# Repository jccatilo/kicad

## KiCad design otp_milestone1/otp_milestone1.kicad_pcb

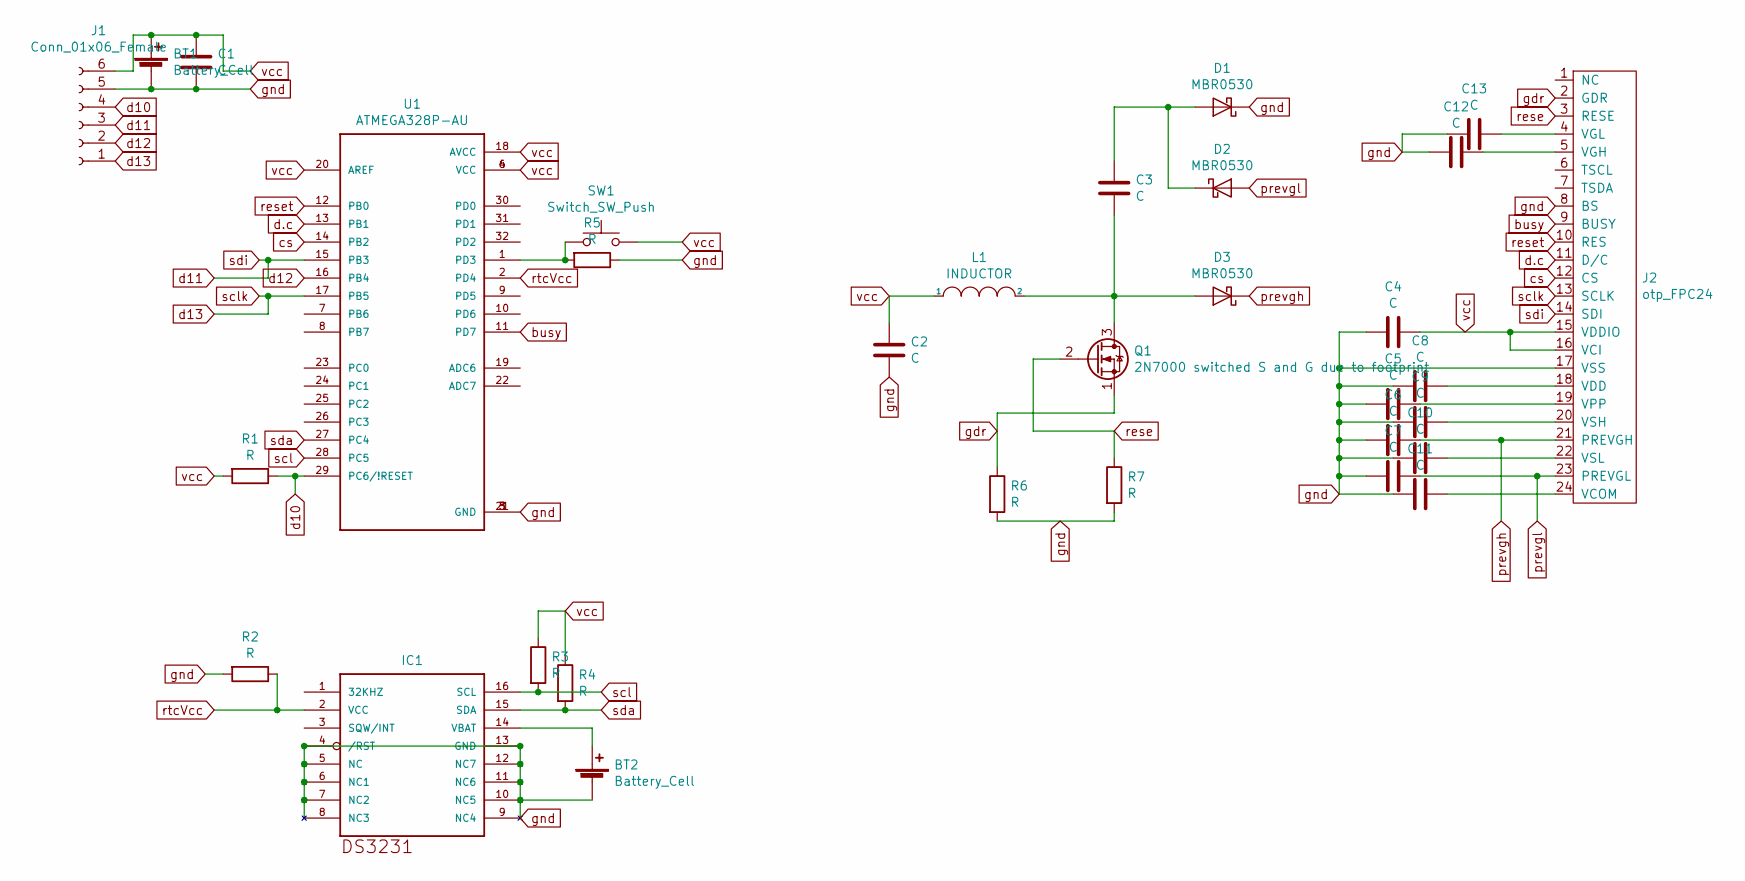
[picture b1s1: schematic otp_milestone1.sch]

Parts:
BT1: Battery_Cell; otp_coincellbattery holder
BT2: Battery_Cell; Conn2
C1, C2, C3, C4, C5, C6, C7, C8, C9, C10, C11, C12, C13: C; C_0805_HandSoldering
D1, D2, D3: MBR0530; D_2010
IC1: DS3231; SO16W
J1: Conn_01x06_Female; conn6
J2: otp_FPC24; FPC24
L1: INDUCTOR; inductorsmd
Q1: 2N7000 switched S and G due to footprint; SOT-23
R1, R2, R3, R4, R5, R6, R7: R; R_0805_HandSoldering
SW1: Switch_SW_Push; pushbutton_2pin
U1: ATMEGA328P-AU; QFP80P900X900X120-32N

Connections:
unnamed: BT2.1 (+), IC1.14 (VBAT)
unnamed: C3.1, D1.2 (A), D2.1 (K)
unnamed: C3.2, D3.2 (A), L1.2, Q1.3 (D)
unnamed: C5.1, J2.19 (VPP)
unnamed: C8.1, J2.18 (VDD)
unnamed: C9.1, J2.20 (VSH)
unnamed: C10.1, J2.22 (VSL)
unnamed: C11.1, J2.24 (VCOM)
unnamed: C12.1, J2.5 (VGH)
unnamed: C13.1, J2.4 (VGL)
unnamed: R5.2, SW1.1, U1.1 (PD3)
busy: J2.9 (BUSY), U1.11 (PD7)
cs: J2.12 (CS), U1.14 (PB2)
d10: J1.4, R1.1, U1.29 (PC6/!RESET)
d11: J1.3, J2.14 (SDI), U1.15 (PB3)
d12: J1.2, U1.16 (PB4)
d13: J1.1, J2.13 (SCLK), U1.17 (PB5)
d.c: J2.11 (D/C), U1.13 (PB1)
gdr: J2.2 (GDR), Q1.1 (S), R6.1
gnd: BT1.2 (-), BT2.2 (-), C1.2, C2.2, C4.2, C5.2, C6.2, C7.2, C8.2, C9.2, C10.2, C11.2, C12.2, C13.2, D1.1 (K), IC1.4 (/RST), IC1.5 (NC), IC1.6 (NC1), IC1.7 (NC2), IC1.8 (NC3), IC1.9 (NC4), IC1.10 (NC5), IC1.11 (NC6), IC1.12 (NC7), IC1.13 (GND), J1.5, J2.8 (BS), J2.17 (VSS), R2.2, R5.1, R6.2, R7.2, U1.3 (GND), U1.5 (GND), U1.21 (GND)
prevgh: C6.1, D3.1 (K), J2.21 (PREVGH)
prevgl: C7.1, D2.2 (A), J2.23 (PREVGL)
rese: J2.3 (RESE), Q1.2 (G), R7.1
reset: J2.10 (RES), U1.12 (PB0)
rtcVcc: IC1.2 (VCC), R2.1, U1.2 (PD4)
scl: IC1.16 (SCL), R3.2, U1.28 (PC5)
sda: IC1.15 (SDA), R4.2, U1.27 (PC4)
vcc: BT1.1 (+), C1.1, C2.1, C4.1, J1.6, J2.15 (VDDIO), J2.16 (VCI), L1.1, R1.2, R3.1, R4.1, SW1.2, U1.4 (VCC), U1.6 (VCC), U1.18 (AVCC), U1.20 (AREF)

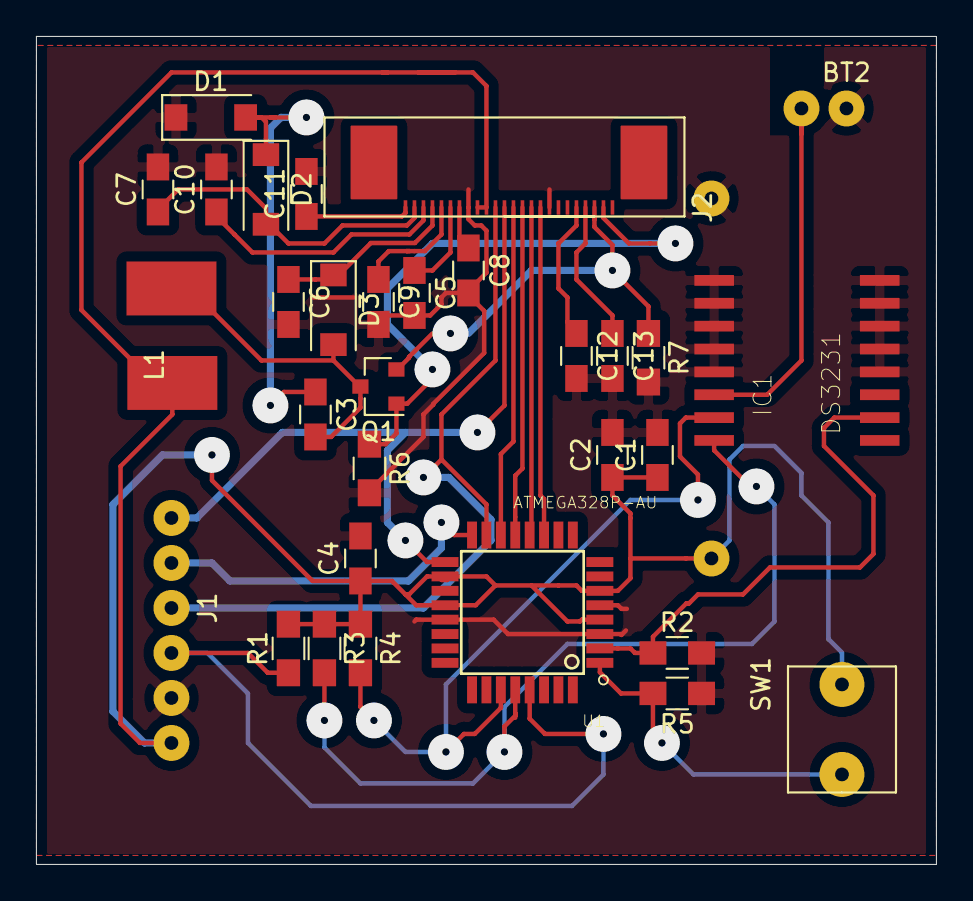
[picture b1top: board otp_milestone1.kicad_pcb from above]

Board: 2 copper layers, 50.0 x 46.0 mm, 32 parts (0 on the bottom side), 28 nets.

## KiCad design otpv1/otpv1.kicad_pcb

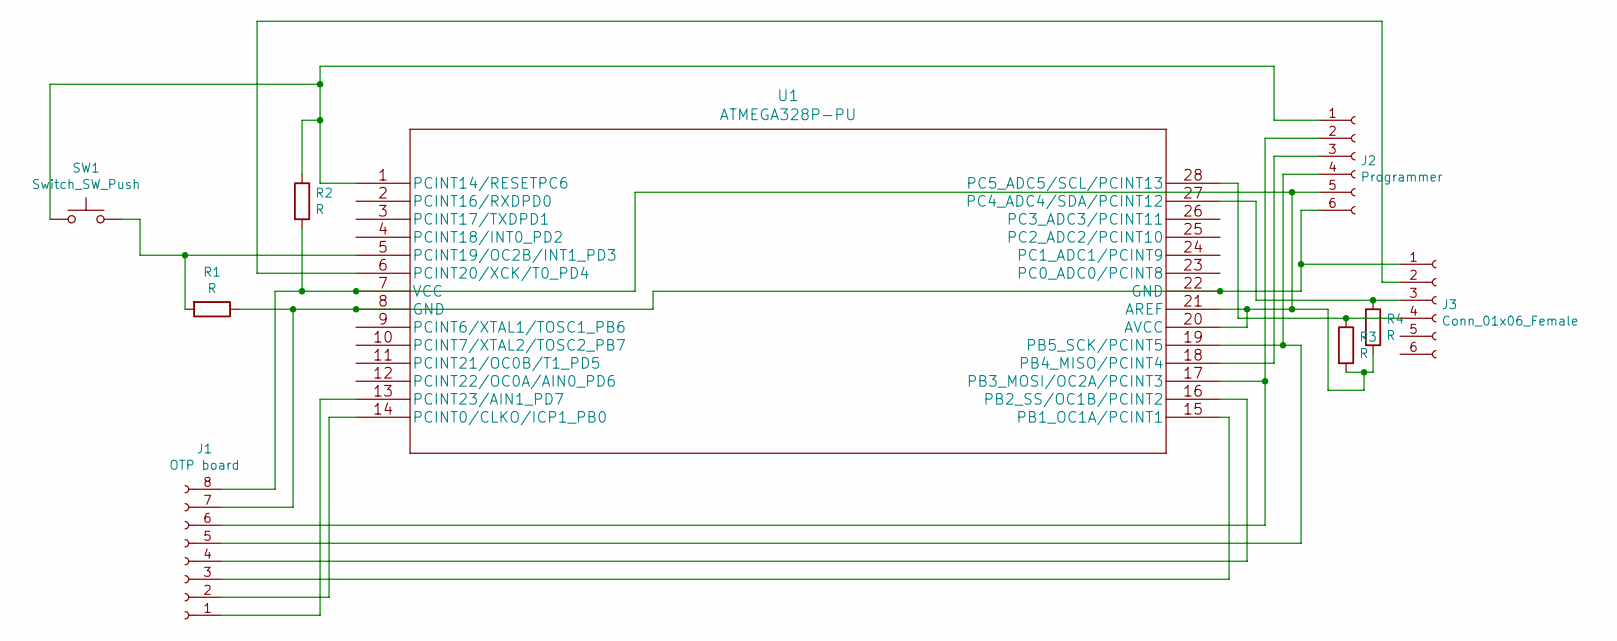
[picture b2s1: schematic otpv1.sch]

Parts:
J1: OTP board; conn8
J2: Programmer; conn6
J3: Conn_01x06_Female; conn6
R1, R2, R3, R4: R; R_0805_HandSoldering
SW1: Switch_SW_Push; pushbutton
U1: ATMEGA328P-PU

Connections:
unnamed: J1.1, U1.13 (PCINT23/AIN1_PD7)
unnamed: J1.2, U1.14 (PCINT0/CLKO/ICP1_PB0)
unnamed: J1.3, U1.15 (PB1_OC1A/PCINT1)
unnamed: J1.4, U1.16 (PB2_SS/OC1B/PCINT2)
unnamed: J1.5, J2.4, U1.19 (PB5_SCK/PCINT5)
unnamed: J1.6, J2.2, U1.17 (PB3_MOSI/OC2A/PCINT3)
unnamed: J1.7, J2.6, J3.1, R1.1, U1.8 (GND), U1.22 (GND)
unnamed: J1.8, J2.5, R2.2, R3.2, R4.2, U1.7 (VCC), U1.20 (AVCC), U1.21 (AREF)
unnamed: J2.1, R2.1, SW1.1, U1.1 (PCINT14/RESETPC6)
unnamed: J2.3, U1.18 (PB4_MISO/PCINT4)
unnamed: J3.2, U1.6 (PCINT20/XCK/T0_PD4)
unnamed: J3.3, R4.1, U1.27 (PC4_ADC4/SDA/PCINT12)
unnamed: J3.4, R3.1, U1.28 (PC5_ADC5/SCL/PCINT13)
unnamed: R1.2, SW1.2, U1.5 (PCINT19/OC2B/INT1_PD3)

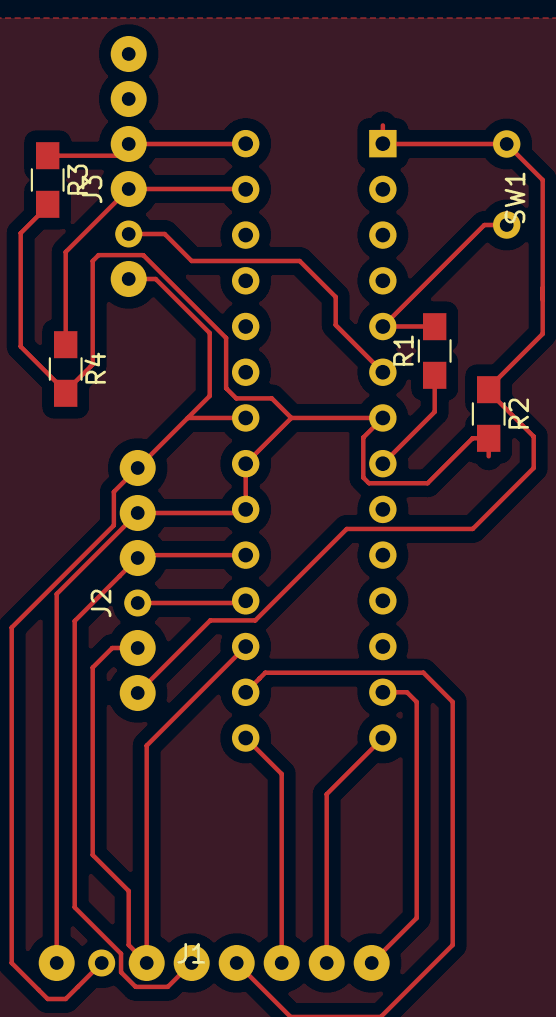
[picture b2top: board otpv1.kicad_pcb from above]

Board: 2 copper layers, 9 parts (1 on the bottom side), 14 nets.

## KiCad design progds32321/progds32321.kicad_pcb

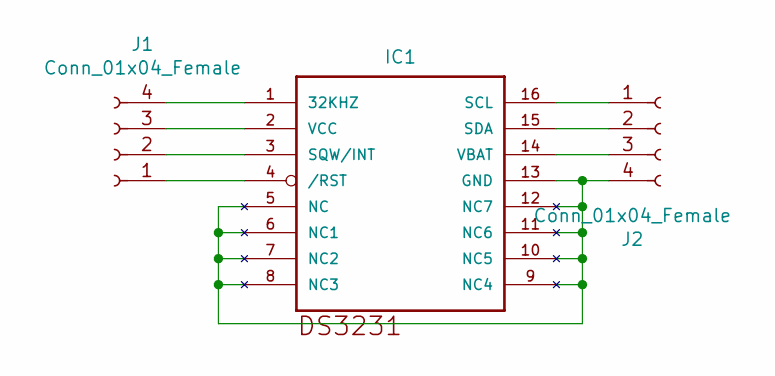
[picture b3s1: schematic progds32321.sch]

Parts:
IC1: DS3231; SO16W
J1, J2: Conn_01x04_Female; Connector4

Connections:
unnamed: IC1.1 (32KHZ), J1.4
unnamed: IC1.2 (VCC), J1.3
unnamed: IC1.3 (SQW/INT), J1.2
unnamed: IC1.4 (/RST), J1.1
unnamed: IC1.5 (NC), IC1.6 (NC1), IC1.7 (NC2), IC1.8 (NC3), IC1.9 (NC4), IC1.10 (NC5), IC1.11 (NC6), IC1.12 (NC7), IC1.13 (GND), J2.4
unnamed: IC1.14 (VBAT), J2.3
unnamed: IC1.15 (SDA), J2.2
unnamed: IC1.16 (SCL), J2.1

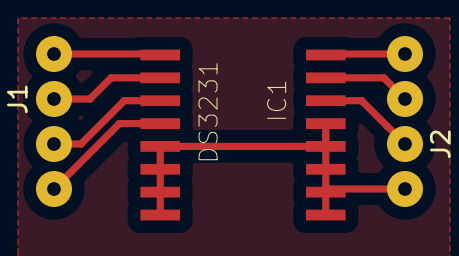
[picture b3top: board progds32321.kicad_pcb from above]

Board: 2 copper layers, 3 parts (0 on the bottom side), 8 nets.

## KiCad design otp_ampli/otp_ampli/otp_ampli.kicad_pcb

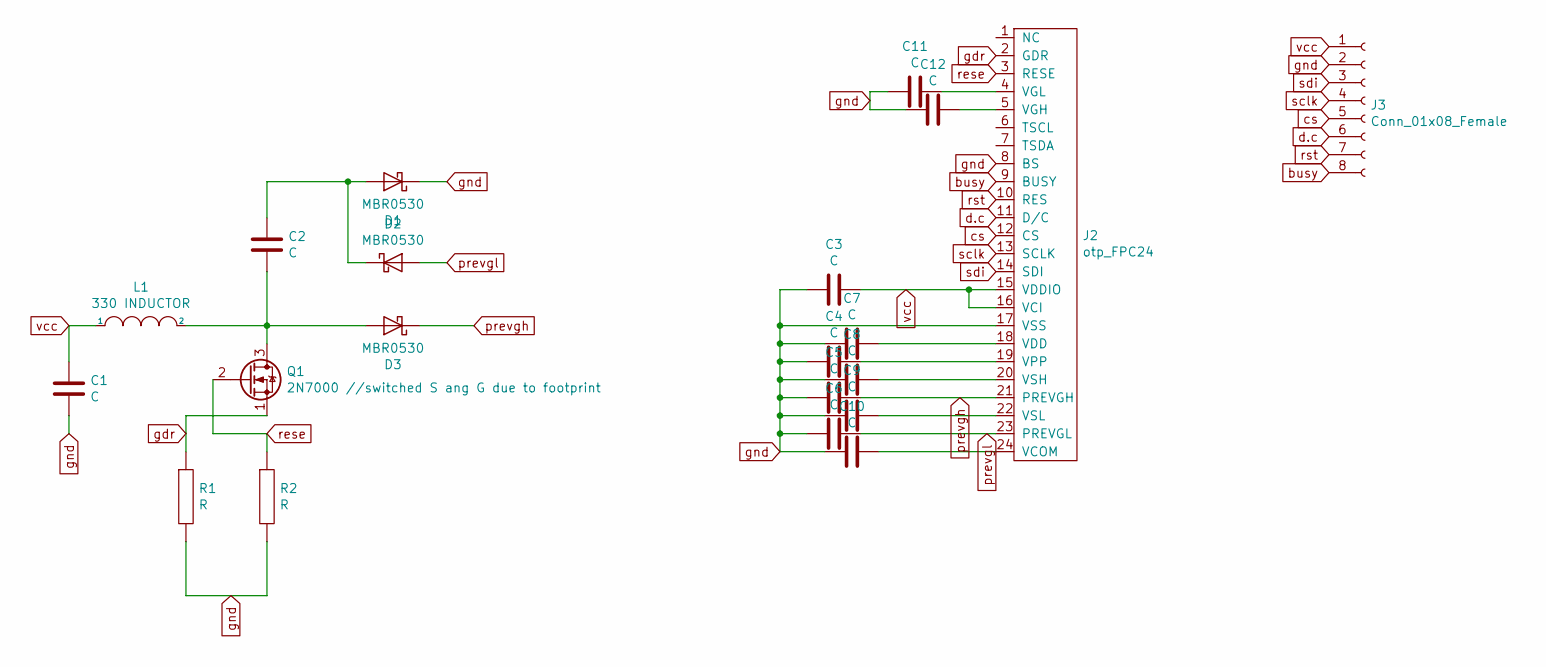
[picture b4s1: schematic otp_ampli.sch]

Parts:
C1, C2, C3, C4, C5, C6, C7, C8, C9, C10, C11, C12: C; C_0805_HandSoldering
D1, D2, D3: MBR0530; D_2010
J2: otp_FPC24; conn_24
J3: Conn_01x08_Female; conn8
L1: 330 INDUCTOR; inductorsmd
Q1: 2N7000 //switched S ang G due to footprint; SOT-23
R1, R2: R; R_0805_HandSoldering

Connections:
unnamed: C2.1, D1.2 (A), D2.1 (K)
unnamed: C2.2, D3.2 (A), L1.2, Q1.3 (D)
unnamed: C4.1, J2.19 (VPP)
unnamed: C7.1, J2.18 (VDD)
unnamed: C8.1, J2.20 (VSH)
unnamed: C9.1, J2.22 (VSL)
unnamed: C10.1, J2.24 (VCOM)
unnamed: C11.1, J2.4 (VGL)
unnamed: C12.1, J2.5 (VGH)
busy: J2.9 (BUSY), J3.8
cs: J2.12 (CS), J3.5
d.c: J2.11 (D/C), J3.6
gdr: J2.2 (GDR), Q1.1 (S), R1.1
gnd: C1.2, C3.2, C4.2, C5.2, C6.2, C7.2, C8.2, C9.2, C10.2, C11.2, C12.2, D1.1 (K), J2.8 (BS), J2.17 (VSS), J3.2, R1.2, R2.2
prevgh: C5.1, D3.1 (K), J2.21 (PREVGH)
prevgl: C6.1, D2.2 (A), J2.23 (PREVGL)
rese: J2.3 (RESE), Q1.2 (G), R2.1
rst: J2.10 (RES), J3.7
sclk: J2.13 (SCLK), J3.4
sdi: J2.14 (SDI), J3.3
vcc: C1.1, C3.1, J2.15 (VDDIO), J2.16 (VCI), J3.1, L1.1

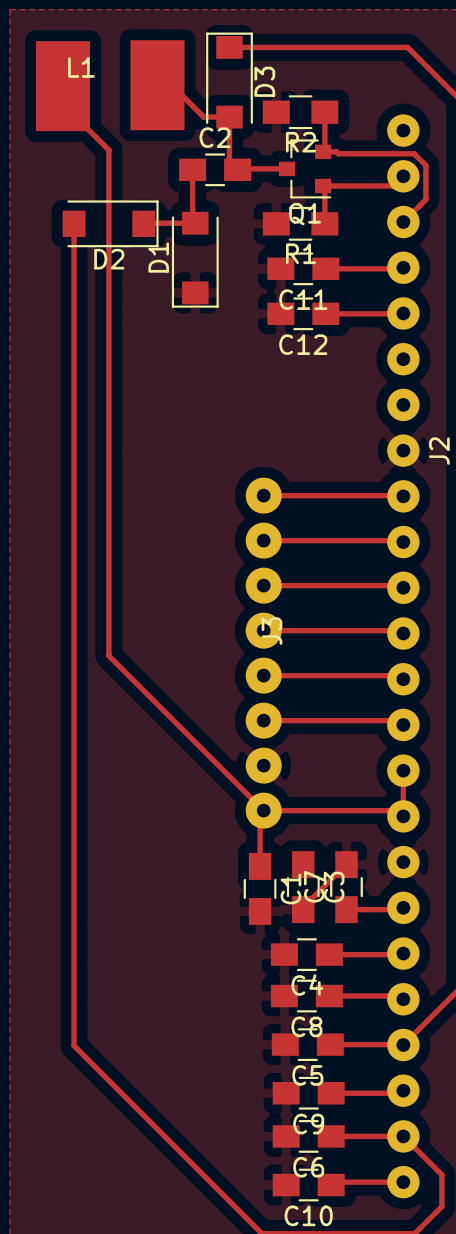
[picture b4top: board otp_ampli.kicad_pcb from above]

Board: 2 copper layers, 21 parts (0 on the bottom side), 21 nets.

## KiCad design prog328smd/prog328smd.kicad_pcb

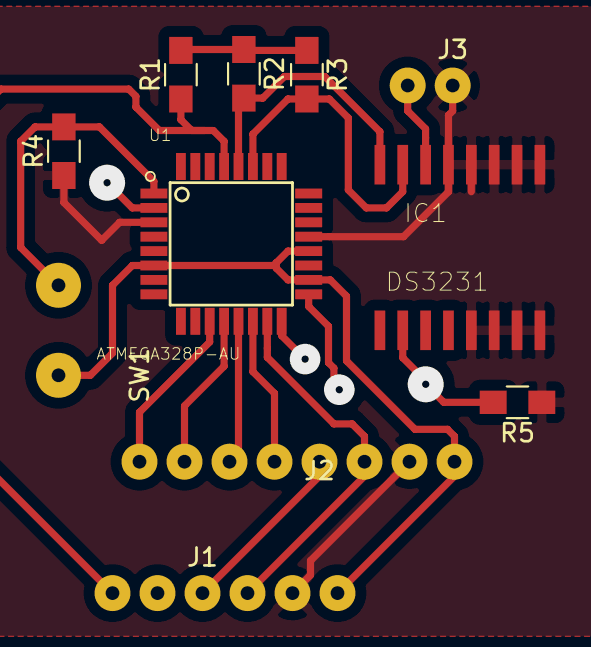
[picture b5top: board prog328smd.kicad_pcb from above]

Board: 2 copper layers, 11 parts (0 on the bottom side), 15 nets.

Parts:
IC1: DS3231; SO16W
J1: Conn_01x06_Female; conn6
J2: Conn_01x08_Female; conn8
J3: Conn_01x02_Female; Conn2
R1, R2, R3, R4, R5: R; R_0805_HandSoldering
SW1: SW_Push; pushbutton_2pin
U1: ATMEGA328P-AU; QFP80P900X900X120-32N

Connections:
unnamed: IC1.14, J3.1
unnamed: R4.2, SW1.1, U1.1
busy: J2.1, U1.11
cs: J2.4, U1.14
d10: J1.1, R1.1, U1.29
d11: J1.4, J2.6, U1.15
d12: J1.2, U1.16
d13: J1.3, J2.5, U1.17
d.c: J2.3, U1.13
gnd: IC1.5, IC1.6, IC1.7, IC1.8, IC1.9, IC1.10, IC1.11, IC1.12, IC1.13, J1.5, J2.7, J3.2, R4.1, R5.1, U1.3, U1.5, U1.21
reset: J2.2, U1.12
rtcVcc: IC1.2, R5.2, U1.2
scl: IC1.16, R2.2, U1.28
sda: IC1.15, R3.2, U1.27
vcc: J1.6, J2.8, R1.2, R2.1, R3.1, SW1.2, U1.4, U1.6, U1.18, U1.20

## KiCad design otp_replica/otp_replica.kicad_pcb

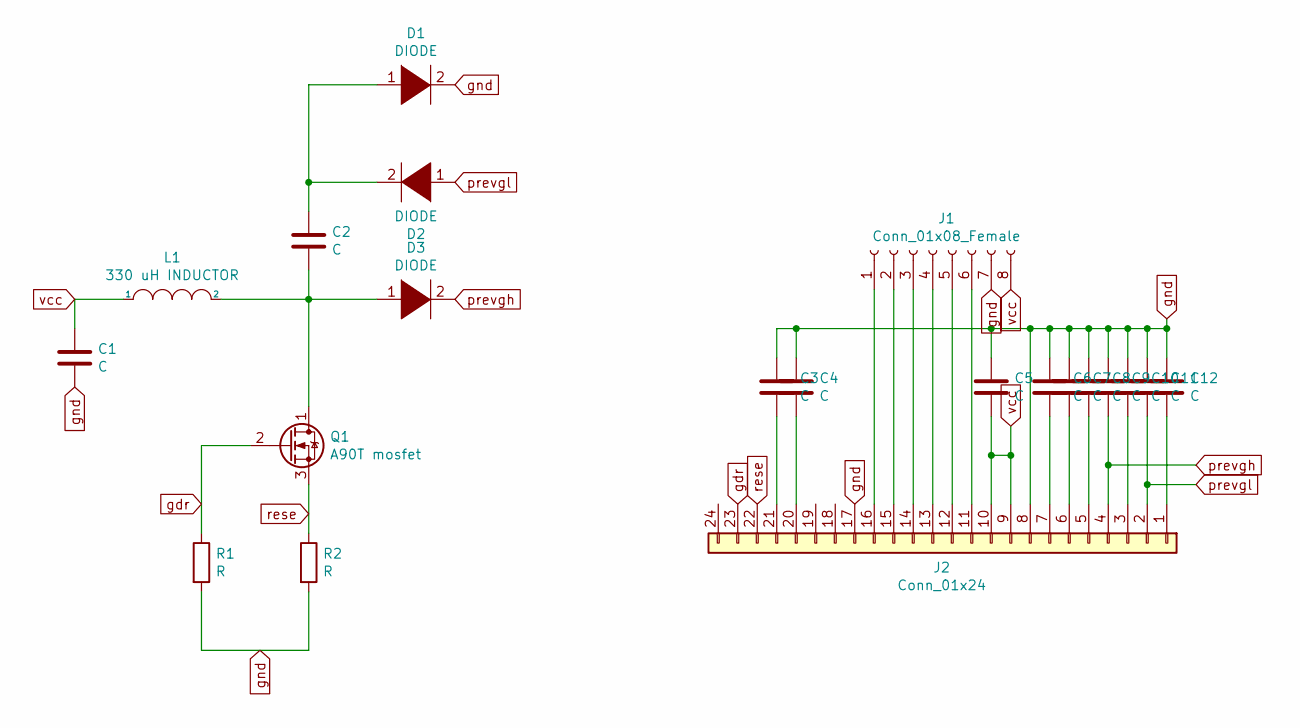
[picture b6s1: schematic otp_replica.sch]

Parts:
C1, C2, C3, C4, C5, C6, C7, C8, C9, C10, C11, C12: C; CP_Radial_D5.0mm_P2.00mm
D1, D2, D3: DIODE; D_0805
J1: Conn_01x08_Female; conn8
J2: Conn_01x24; conn_24
L1: 330 uH INDUCTOR; L_6.3x6.3_H3
Q1: A90T mosfet; OldSowjetaera_Transistor_Type-I_BigPads
R1, R2: R; R_0805_HandSoldering

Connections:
unnamed: C2.1, D1.1 (K), D2.2 (A)
unnamed: C2.2, D3.1 (K), L1.2, Q1.1 (D)
unnamed: C3.2, J2.21
unnamed: C4.2, J2.20
unnamed: C6.2, J2.7
unnamed: C7.2, J2.6
unnamed: C8.2, J2.5
unnamed: C10.2, J2.3
unnamed: C12.2, J2.1
unnamed: J1.1, J2.16
unnamed: J1.2, J2.15
unnamed: J1.3, J2.14
unnamed: J1.4, J2.13
unnamed: J1.5, J2.12
unnamed: J1.6, J2.11
gdr: J2.23, Q1.2 (G), R1.1
gnd: C1.2, C3.1, C4.1, C5.1, C6.1, C7.1, C8.1, C9.1, C10.1, C11.1, C12.1, D1.2 (A), J1.7, J2.8, J2.17, R1.2, R2.2
prevgh: C9.2, D3.2 (A), J2.4
prevgl: C11.2, D2.1 (K), J2.2
rese: J2.22, Q1.3 (S), R2.1
vcc: C1.1, C5.2, J1.8, J2.9, J2.10, L1.1

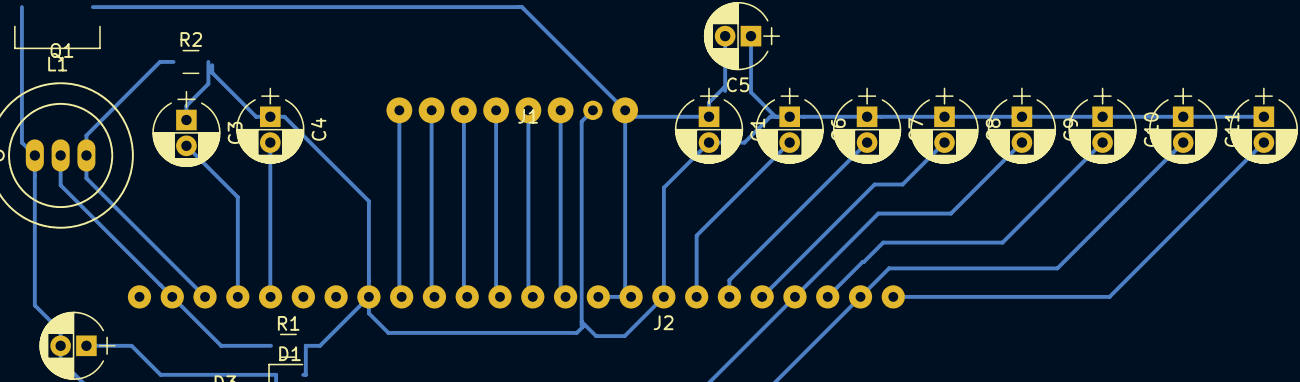
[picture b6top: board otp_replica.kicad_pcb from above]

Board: 2 copper layers, 21 parts (0 on the bottom side), 21 nets.

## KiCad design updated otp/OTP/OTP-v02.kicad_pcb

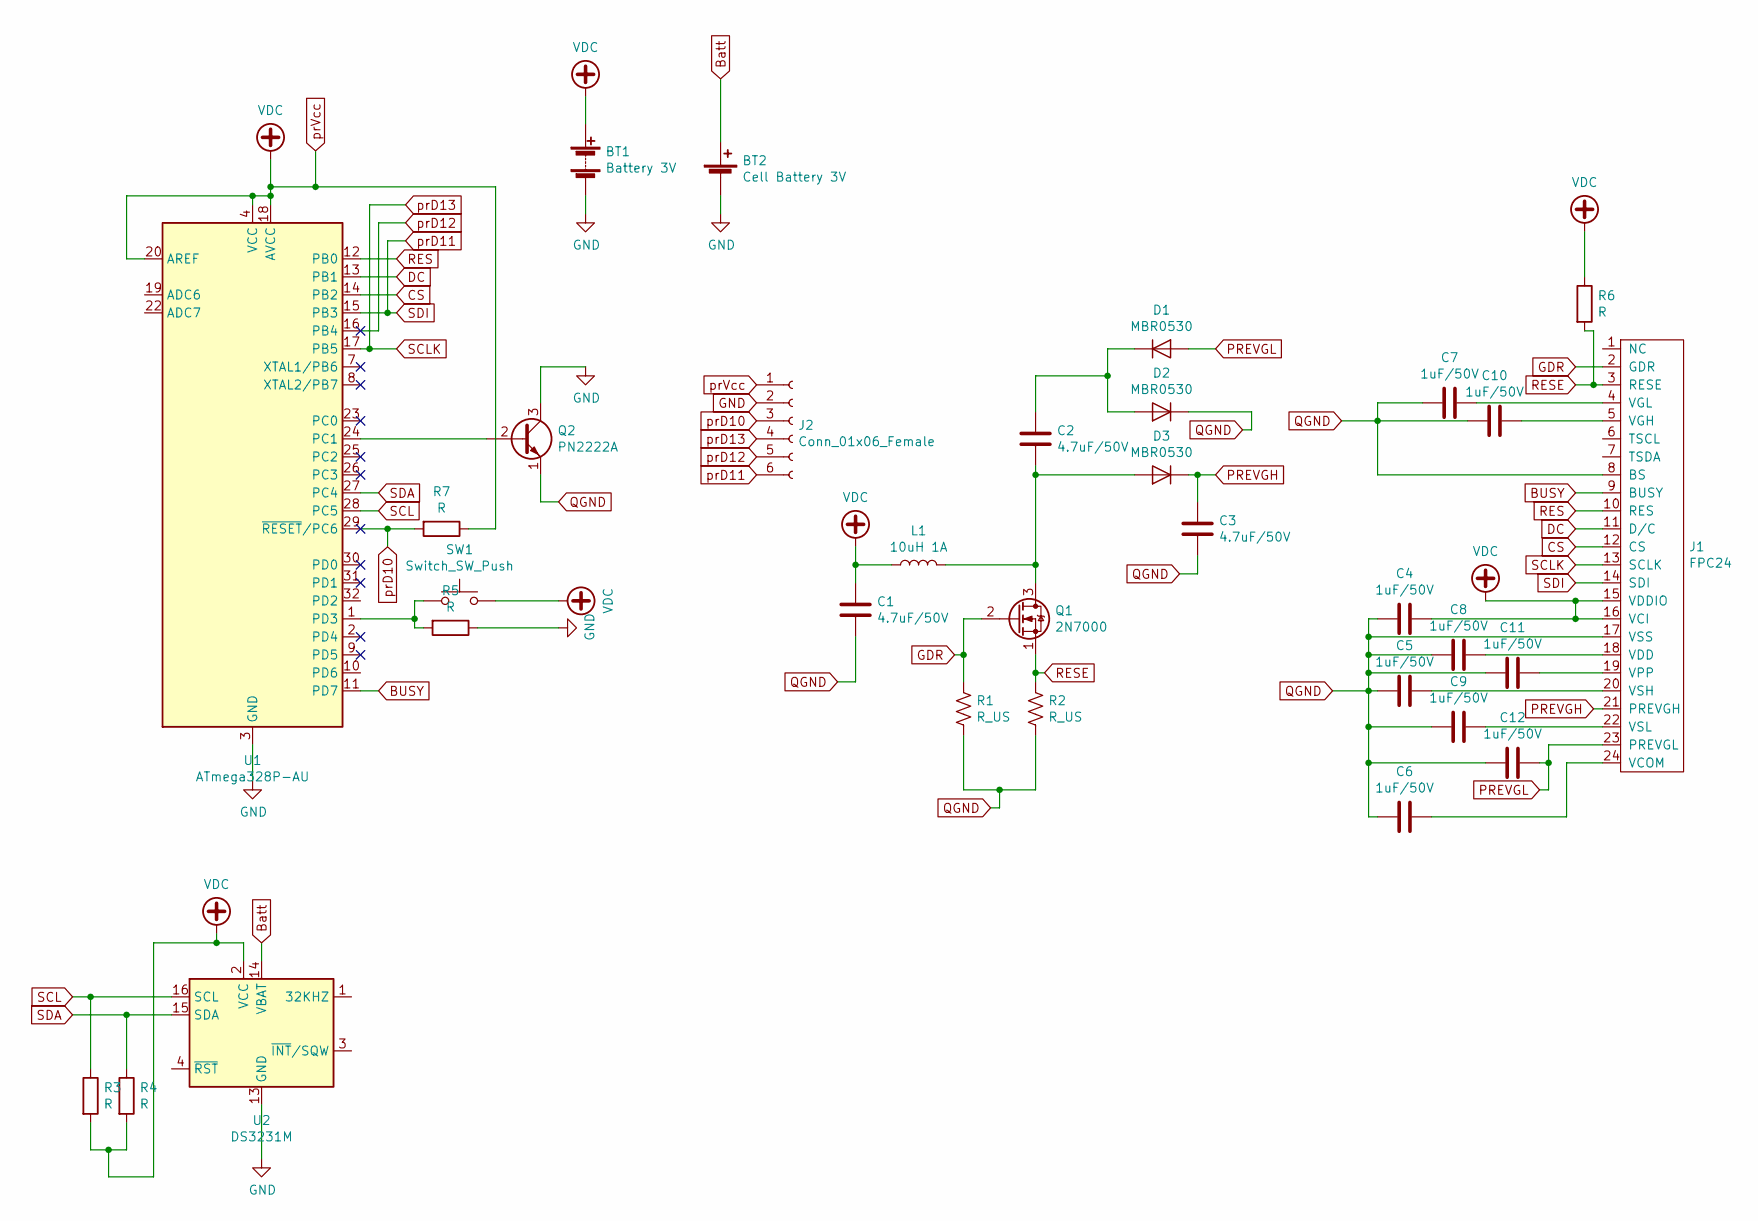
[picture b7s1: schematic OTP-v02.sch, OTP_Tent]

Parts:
BT1: Battery 3V; Battery_pack_connector
BT2: Cell Battery 3V; Cell Battery SMD
C1, C2, C3: 4.7uF/50V; C_0805_2012Metric_Pad1.15x1.40mm_HandSolder
C4, C5, C6, C7, C8, C9, C10, C11, C12: 1uF/50V; C_0805_2012Metric_Pad1.15x1.40mm_HandSolder
D1, D2, D3: MBR0530; D_SOD-123
J1: FPC24
J2: Conn_01x06_Female; programmer06
L1: 10uH 1A; CD54
Q1: 2N7000; SOT-23
Q2: PN2222A; SOT-23
R1, R2: R_US; R_0805_2012Metric_Pad1.15x1.40mm_HandSolder
R3, R4, R5, R6: R; C_0805_HandSoldering
R7: R; C_0805_2012Metric_Pad1.15x1.40mm_HandSolder
SW1: Switch_SW_Push; pushbutton_2pin
U1: ATmega328P-AU; TQFP-32_7x7mm_P0.8mm
U2: DS3231M; SOIC-16W_7.5x10.3mm_P1.27mm

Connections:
BUSY: J1.9 (BUSY), U1.11 (PD7)
Batt: BT2.1 (+), U2.14 (VBAT)
CS: J1.12 (CS), U1.14 (PB2)
DC: J1.11 (D/C), U1.13 (PB1)
GDR: J1.2 (GDR), Q1.2 (G), R1.1
GND: BT1.2 (-), BT2.2 (-), J2.2, Q2.3 (C), R5.1, U1.3 (GND), U1.5 (GND), U1.21 (GND), U2.5 (GND), U2.6 (GND), U2.7 (GND), U2.8 (GND), U2.9 (GND), U2.10 (GND), U2.11 (GND), U2.12 (GND), U2.13 (GND)
unnamed: C2.1, D1.1 (K), D2.2 (A)
unnamed: C2.2, D3.2 (A), L1.2, Q1.3 (D)
unnamed: C5.1, J1.20 (VSH)
unnamed: C6.1, J1.24 (VCOM)
unnamed: C7.1, J1.4 (VGL)
unnamed: C8.1, J1.18 (VDD)
unnamed: C9.1, J1.22 (VSL)
unnamed: C10.1, J1.5 (VGH)
unnamed: C11.1, J1.19 (VPP)
unnamed: Q2.2 (B), U1.24 (PC1)
unnamed: R5.2, SW1.1, U1.1 (PD3)
PREVGH: C3.1, D3.1 (K), J1.21 (PREVGH)
PREVGL: C12.1, D1.2 (A), J1.23 (PREVGL)
QGND: C1.2, C3.2, C4.2, C5.2, C6.2, C7.2, C8.2, C9.2, C10.2, C11.2, C12.2, D2.1 (K), J1.8 (BS), J1.17 (VSS), Q2.1 (E), R1.2, R2.2
RES: J1.10 (RES), U1.12 (PB0)
RESE: J1.3 (RESE), Q1.1 (S), R2.1, R6.2
SCL: R3.1, U1.28 (PC5), U2.16 (SCL)
SCLK: J1.13 (SCLK), J2.4, U1.17 (PB5)
SDA: R4.1, U1.27 (PC4), U2.15 (SDA)
SDI: J1.14 (SDI), J2.6, U1.15 (PB3)
prD10: J2.3, R7.2, U1.29 (~RESET~/PC6)
prD12: J2.5, U1.16 (PB4)
prVcc: BT1.1 (+), C1.1, C4.1, J1.15 (VDDIO), J1.16 (VCI), J2.1, L1.1, R3.2, R4.2, R6.1, R7.1, SW1.2, U1.4 (VCC), U1.6 (VCC), U1.18 (AVCC), U1.20 (AREF), U2.2 (VCC)

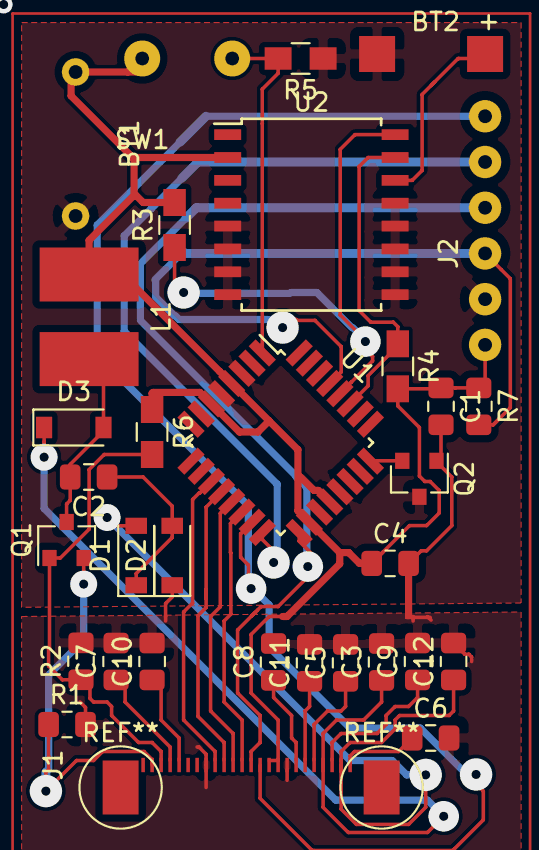
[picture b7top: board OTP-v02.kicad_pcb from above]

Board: 2 copper layers, 32 parts (0 on the bottom side), 29 nets.

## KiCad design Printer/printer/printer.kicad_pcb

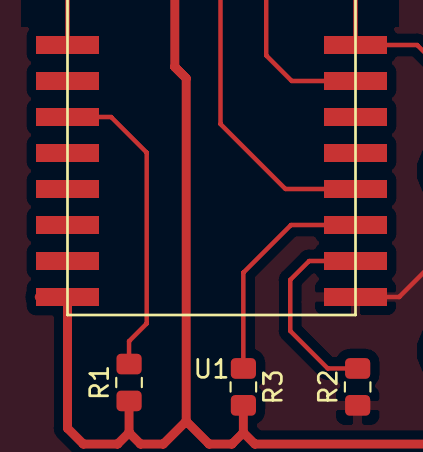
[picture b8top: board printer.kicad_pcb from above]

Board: 2 copper layers, 4 parts (0 on the bottom side), 5 nets.

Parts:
R1, R2, R3: 10K; C_0805_2012Metric_Pad1.15x1.40mm_HandSolder
U1: ESP-12F; esp-12

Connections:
+3V3: R1.1, R3.2, U1.15
GND: R2.1, U1.8
unnamed: R1.2, U1.20
unnamed: R2.2, U1.7
unnamed: R3.1, U1.6

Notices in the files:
otp_mod/OTP/OTP-v02.sch:
License: For Internal Use Only
parts and their libraries:
Copyright 2016 Accelerated Designs. All rights reserved.
